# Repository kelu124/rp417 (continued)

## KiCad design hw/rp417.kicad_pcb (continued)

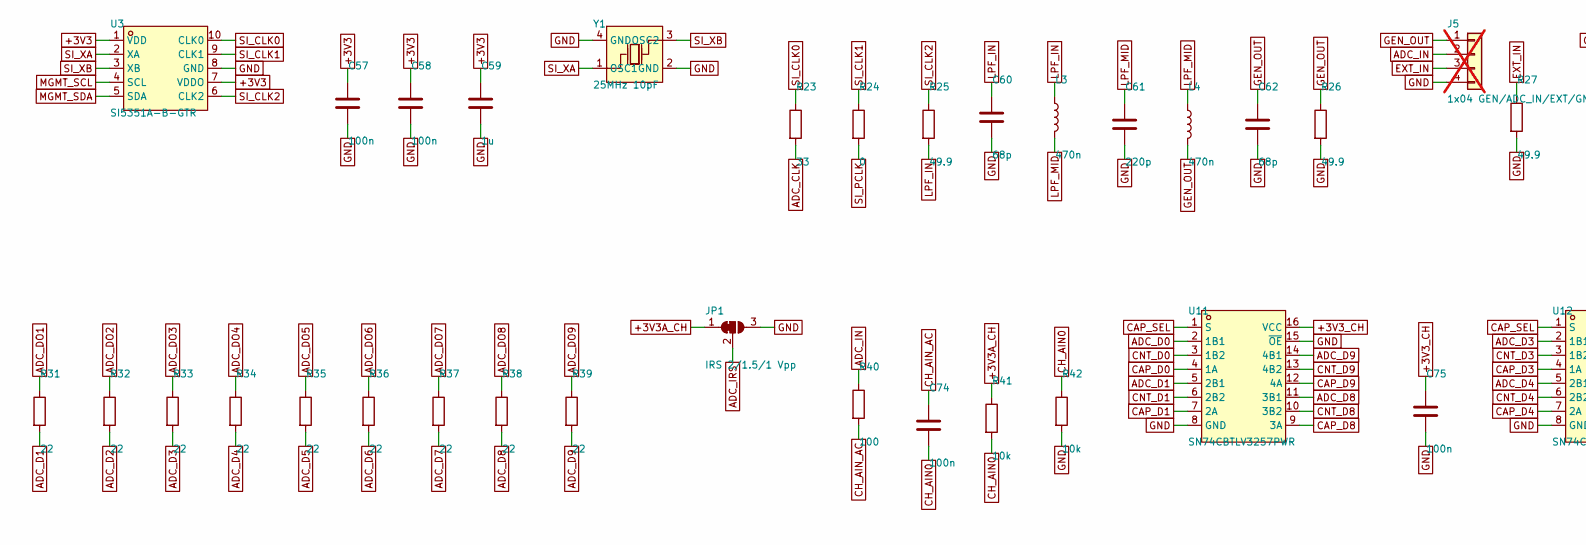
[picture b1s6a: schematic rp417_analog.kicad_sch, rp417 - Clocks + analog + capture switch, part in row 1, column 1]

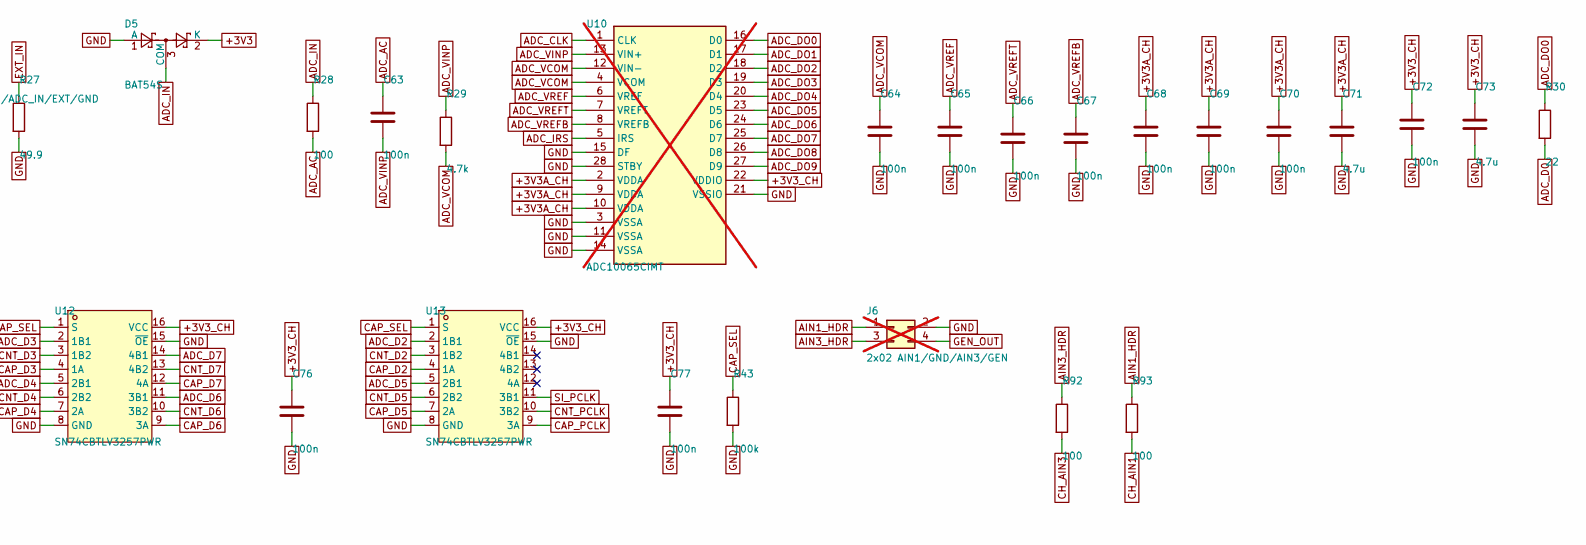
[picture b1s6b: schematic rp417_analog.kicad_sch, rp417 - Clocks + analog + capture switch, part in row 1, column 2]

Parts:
C57, C58, C63, C64, C65, C66, C67, C68, C69, C70, C72, C74, C75, C76, C77: 100n; C_0402_1005Metric; MPN 100n; LCSC C307331
C59: 1u; C_0402_1005Metric; MPN 1u; LCSC C52923
C60, C62: 68p; C_0402_1005Metric; MPN 68p; LCSC C14441
C61: 220p; C_0402_1005Metric; MPN 220p; LCSC C1513258
C71, C73: 4.7u; C_0603_1608Metric; MPN 4.7u; LCSC C19666
D5: BAT54S; SOT-23; MPN BAT54S; LCSC C8592
J5: 1x04 GEN/ADC_IN/EXT/GND; PinHeader_1x04_P2.54mm_Vertical; MPN 1x04 GEN/ADC_IN/EXT/GND; not fitted
J6: 2x02 AIN1/GND/AIN3/GEN; PinHeader_2x02_P2.54mm_Vertical; MPN 2x02 AIN1/GND/AIN3/GEN; not fitted
JP1: IRS 2/1.5/1 Vpp; SolderJumper-3_P1.3mm_Bridged12_RoundedPad1.0x1.5mm; MPN IRS 2/1.5/1 Vpp
L3, L4: 470n; L_0603_1608Metric; MPN LQW18ANR47G00D; LCSC C113132
R23: 33; R_0402_1005Metric; MPN 33; LCSC C25105
R24: 0; R_0402_1005Metric; MPN 0; LCSC C17168
R25, R26, R27: 49.9; R_0402_1005Metric; MPN 49.9; LCSC C25120
R28, R40, R92, R93: 100; R_0402_1005Metric; MPN 100; LCSC C25076
R29: 4.7k; R_0402_1005Metric; MPN 4.7k; LCSC C25900
R30, R31, R32, R33, R34, R35, R36, R37, R38, R39: 22; R_0402_1005Metric; MPN 22; LCSC C25092
R41, R42: 10k; R_0402_1005Metric; MPN 10k; LCSC C25744
R43: 100k; R_0402_1005Metric; MPN 100k; LCSC C25741
U3: SI5351A-B-GTR; MSOP-10_L3.0-W3.0-P0.50-LS5.0-BL; MPN SI5351A-B-GTR; LCSC C504891
U10: ADC10065CIMT; TSSOP-28_4.4x9.7mm_P0.65mm; MPN ADC10065CIMT/NOPB (DNP, user-fitted, D4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; LCSC C1542621; not fitted
U11, U12, U13: SN74CBTLV3257PWR; TSSOP-16_L5.0-W4.4-P0.65-LS6.4-BL; MPN SN74CBTLV3257PWR; LCSC C7637
Y1: 25MHz 10pF; CRYSTAL-SMD_4P-L3.2-W2.5-BL; MPN X322525MMB4SI; LCSC C70582

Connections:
+3V3: C57.1, C58.1, C59.1, D5.2 (K), U3.1 (VDD), U3.7 (VDDO); also elsewhere on the board
+3V3A_CH: C68.1, C69.1, C70.1, C71.1, JP1.1 (A), R41.1, U10.2 (VDDA), U10.9 (VDDA), U10.10 (VDDA); also elsewhere on the board
+3V3_CH: C72.1, C73.1, C75.1, C76.1, C77.1, U10.22 (VDDIO), U11.16 (VCC), U12.16 (VCC), U13.16 (VCC); also elsewhere on the board
ADC_AC: C63.1, R28.2
ADC_CLK: R23.2, U10.1 (CLK)
ADC_D0: R30.2, U11.2 (1B1)
ADC_D1: R31.2, U11.5 (2B1)
ADC_D2: R32.2, U13.2 (1B1)
ADC_D3: R33.2, U12.2 (1B1)
ADC_D4: R34.2, U12.5 (2B1)
ADC_D5: R35.2, U13.5 (2B1)
ADC_D6: R36.2, U12.11 (3B1)
ADC_D7: R37.2, U12.14 (4B1)
ADC_D8: R38.2, U11.11 (3B1)
ADC_D9: R39.2, U11.14 (4B1)
ADC_DO0: R30.1, U10.16 (D0)
ADC_DO1: R31.1, U10.17 (D1)
ADC_DO2: R32.1, U10.18 (D2)
ADC_DO3: R33.1, U10.19 (D3)
ADC_DO4: R34.1, U10.20 (D4)
ADC_DO5: R35.1, U10.23 (D5)
ADC_DO6: R36.1, U10.24 (D6)
ADC_DO7: R37.1, U10.25 (D7)
ADC_DO8: R38.1, U10.26 (D8)
ADC_DO9: R39.1, U10.27 (D9)
ADC_IN: D5.3 (COM), J5.2, R28.1, R40.1
ADC_IRS: JP1.2 (C), U10.5 (IRS)
ADC_VCOM: C64.1, R29.2, U10.4 (VCOM), U10.12 (VIN-)
ADC_VINP: C63.2, R29.1, U10.13 (VIN+)
ADC_VREF: C65.1, U10.6 (VREF)
ADC_VREFB: C67.1, U10.8 (VREFB)
ADC_VREFT: C66.1, U10.7 (VREFT)
AIN1_HDR: J6.1, R93.1
AIN3_HDR: J6.3, R92.1
CAP_D0: U11.4 (1A); also elsewhere on the board
CAP_D1: U11.7 (2A); also elsewhere on the board
CAP_D2: U13.4 (1A); also elsewhere on the board
CAP_D3: U12.4 (1A); also elsewhere on the board
CAP_D4: U12.7 (2A); also elsewhere on the board
CAP_D5: U13.7 (2A); also elsewhere on the board
CAP_D6: U12.9 (3A); also elsewhere on the board
CAP_D7: U12.12 (4A); also elsewhere on the board
CAP_D8: U11.9 (3A); also elsewhere on the board
CAP_D9: U11.12 (4A); also elsewhere on the board
CAP_PCLK: U13.9 (3A); also elsewhere on the board
CAP_SEL: R43.1, U11.1 (S), U12.1 (S), U13.1 (S); also elsewhere on the board
CH_AIN0: C74.2, R41.2, R42.1; also elsewhere on the board
CH_AIN1: R93.2; also elsewhere on the board
CH_AIN3: R92.2; also elsewhere on the board
CH_AIN_AC: C74.1, R40.2
CNT_D0: U11.3 (1B2); also elsewhere on the board
CNT_D1: U11.6 (2B2); also elsewhere on the board
CNT_D2: U13.3 (1B2); also elsewhere on the board
CNT_D3: U12.3 (1B2); also elsewhere on the board
CNT_D4: U12.6 (2B2); also elsewhere on the board
CNT_D5: U13.6 (2B2); also elsewhere on the board
CNT_D6: U12.10 (3B2); also elsewhere on the board
CNT_D7: U12.13 (4B2); also elsewhere on the board
CNT_D8: U11.10 (3B2); also elsewhere on the board
CNT_D9: U11.13 (4B2); also elsewhere on the board
CNT_PCLK: U13.10 (3B2); also elsewhere on the board
EXT_IN: J5.3, R27.1
GEN_OUT: C62.1, J5.1, J6.4, L4.2, R26.1
GND: C57.2, C58.2, C59.2, C60.2, C61.2, C62.2, C64.2, C65.2, C66.2, C67.2, C68.2, C69.2, C70.2, C71.2, C72.2, C73.2, C75.2, C76.2, C77.2, D5.1 (A), J5.4, J6.2, JP1.3 (B), R26.2, R27.2, R42.2, R43.2, U3.8 (GND), U10.3 (VSSA), U10.11 (VSSA), U10.14 (VSSA), U10.15 (DF), U10.21 (VSSIO), U10.28 (STBY), U11.8 (GND), U11.15 (~OE), U12.8 (GND), U12.15 (~OE), U13.8 (GND), U13.15 (~OE), Y1.2 (GND), Y1.4 (GND); also elsewhere on the board
LPF_IN: C60.1, L3.1, R25.2
LPF_MID: C61.1, L3.2, L4.1
MGMT_SCL: U3.4 (SCL); also elsewhere on the board
MGMT_SDA: U3.5 (SDA); also elsewhere on the board
SI_CLK0: R23.1, U3.10 (CLK0)
SI_CLK1: R24.1, U3.9 (CLK1)
SI_CLK2: R25.1, U3.6 (CLK2)
SI_PCLK: R24.2, U13.11 (3B1)
SI_XA: U3.2 (XA), Y1.1 (OSC1)
SI_XB: U3.3 (XB), Y1.3 (OSC2)

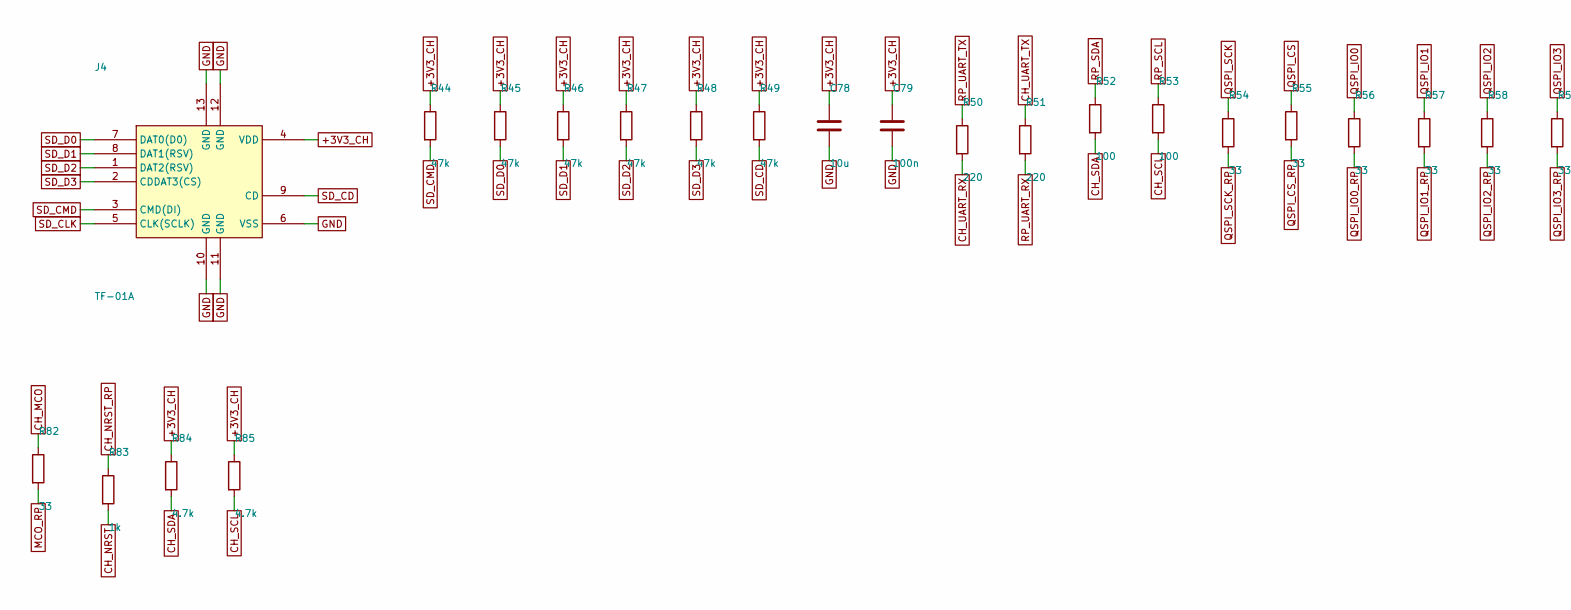
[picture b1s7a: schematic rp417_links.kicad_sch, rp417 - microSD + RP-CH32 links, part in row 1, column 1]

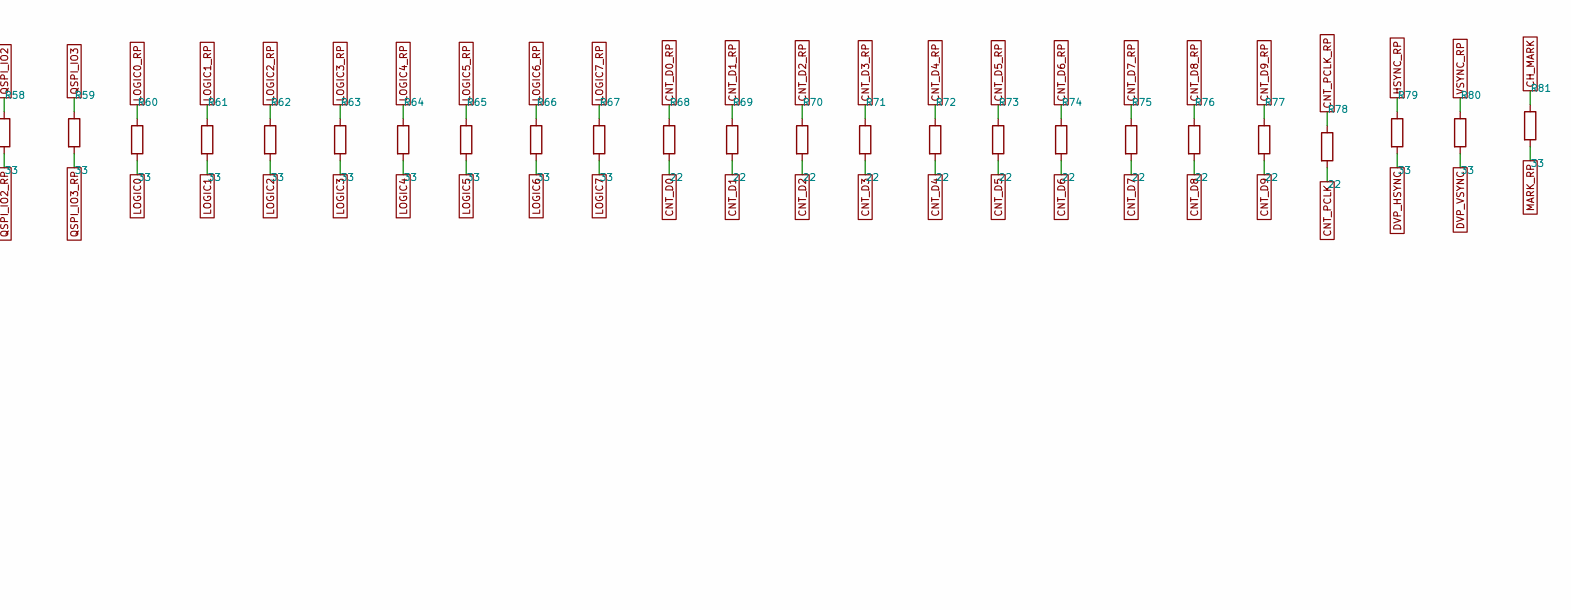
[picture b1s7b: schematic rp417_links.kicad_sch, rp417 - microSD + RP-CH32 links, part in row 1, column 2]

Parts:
C78: 10u; C_0603_1608Metric; MPN 10u; LCSC C96446
C79: 100n; C_0402_1005Metric; MPN 100n; LCSC C307331
J4: TF-01A; TF-SMD_TF-01A; MPN TF-01A; LCSC C91145
R44, R45, R46, R47, R48, R49: 47k; R_0402_1005Metric; MPN 47k; LCSC C25792
R50, R51: 220; R_0402_1005Metric; MPN 220; LCSC C25091
R52, R53: 100; R_0402_1005Metric; MPN 100; LCSC C25076
R54, R55, R56, R57, R58, R59, R60, R61, R62, R63, R64, R65, R66, R67, R79, R80, R81, R82: 33; R_0402_1005Metric; MPN 33; LCSC C25105
R68, R69, R70, R71, R72, R73, R74, R75, R76, R77, R78: 22; R_0402_1005Metric; MPN 22; LCSC C25092
R83: 1k; R_0402_1005Metric; MPN 1k; LCSC C11702
R84, R85: 4.7k; R_0402_1005Metric; MPN 4.7k; LCSC C25900

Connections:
+3V3_CH: C78.1, C79.1, J4.4 (VDD), R44.1, R45.1, R46.1, R47.1, R48.1, R49.1, R84.1, R85.1; also elsewhere on the board
CH_MARK: R81.1; also elsewhere on the board
CH_MCO: R82.1; also elsewhere on the board
CH_NRST: R83.2; also elsewhere on the board
CH_NRST_RP: R83.1; also elsewhere on the board
CH_SCL: R53.2, R85.2; also elsewhere on the board
CH_SDA: R52.2, R84.2; also elsewhere on the board
CH_UART_RX: R50.2; also elsewhere on the board
CH_UART_TX: R51.1; also elsewhere on the board
CNT_D0: R68.2; also elsewhere on the board
CNT_D0_RP: R68.1; also elsewhere on the board
CNT_D1: R69.2; also elsewhere on the board
CNT_D1_RP: R69.1; also elsewhere on the board
CNT_D2: R70.2; also elsewhere on the board
CNT_D2_RP: R70.1; also elsewhere on the board
CNT_D3: R71.2; also elsewhere on the board
CNT_D3_RP: R71.1; also elsewhere on the board
CNT_D4: R72.2; also elsewhere on the board
CNT_D4_RP: R72.1; also elsewhere on the board
CNT_D5: R73.2; also elsewhere on the board
CNT_D5_RP: R73.1; also elsewhere on the board
CNT_D6: R74.2; also elsewhere on the board
CNT_D6_RP: R74.1; also elsewhere on the board
CNT_D7: R75.2; also elsewhere on the board
CNT_D7_RP: R75.1; also elsewhere on the board
CNT_D8: R76.2; also elsewhere on the board
CNT_D8_RP: R76.1; also elsewhere on the board
CNT_D9: R77.2; also elsewhere on the board
CNT_D9_RP: R77.1; also elsewhere on the board
CNT_PCLK: R78.2; also elsewhere on the board
CNT_PCLK_RP: R78.1; also elsewhere on the board
DVP_HSYNC: R79.2; also elsewhere on the board
DVP_VSYNC: R80.2; also elsewhere on the board
GND: C78.2, C79.2, J4.6 (VSS), J4.10 (GND), J4.11 (GND), J4.12 (GND), J4.13 (GND); also elsewhere on the board
HSYNC_RP: R79.1; also elsewhere on the board
LOGIC0: R60.2; also elsewhere on the board
LOGIC0_RP: R60.1; also elsewhere on the board
LOGIC1: R61.2; also elsewhere on the board
LOGIC1_RP: R61.1; also elsewhere on the board
LOGIC2: R62.2; also elsewhere on the board
LOGIC2_RP: R62.1; also elsewhere on the board
LOGIC3: R63.2; also elsewhere on the board
LOGIC3_RP: R63.1; also elsewhere on the board
LOGIC4: R64.2; also elsewhere on the board
LOGIC4_RP: R64.1; also elsewhere on the board
LOGIC5: R65.2; also elsewhere on the board
LOGIC5_RP: R65.1; also elsewhere on the board
LOGIC6: R66.2; also elsewhere on the board
LOGIC6_RP: R66.1; also elsewhere on the board
LOGIC7: R67.2; also elsewhere on the board
LOGIC7_RP: R67.1; also elsewhere on the board
MARK_RP: R81.2; also elsewhere on the board
MCO_RP: R82.2; also elsewhere on the board
QSPI_CS: R55.1; also elsewhere on the board
QSPI_CS_RP: R55.2; also elsewhere on the board
QSPI_IO0: R56.1; also elsewhere on the board
QSPI_IO0_RP: R56.2; also elsewhere on the board
QSPI_IO1: R57.1; also elsewhere on the board
QSPI_IO1_RP: R57.2; also elsewhere on the board
QSPI_IO2: R58.1; also elsewhere on the board
QSPI_IO2_RP: R58.2; also elsewhere on the board
QSPI_IO3: R59.1; also elsewhere on the board
QSPI_IO3_RP: R59.2; also elsewhere on the board
QSPI_SCK: R54.1; also elsewhere on the board
QSPI_SCK_RP: R54.2; also elsewhere on the board
RP_SCL: R53.1; also elsewhere on the board
RP_SDA: R52.1; also elsewhere on the board
RP_UART_RX: R51.2; also elsewhere on the board
RP_UART_TX: R50.1; also elsewhere on the board
SD_CD: J4.9 (CD), R49.2; also elsewhere on the board
SD_CLK: J4.5 (CLK(SCLK)); also elsewhere on the board
SD_CMD: J4.3 (CMD(DI)), R44.2; also elsewhere on the board
SD_D0: J4.7 (DAT0(D0)), R45.2; also elsewhere on the board
SD_D1: J4.8 (DAT1(RSV)), R46.2; also elsewhere on the board
SD_D2: J4.1 (DAT2(RSV)), R47.2; also elsewhere on the board
SD_D3: J4.2 (CDDAT3(CS)), R48.2; also elsewhere on the board
VSYNC_RP: R80.1; also elsewhere on the board

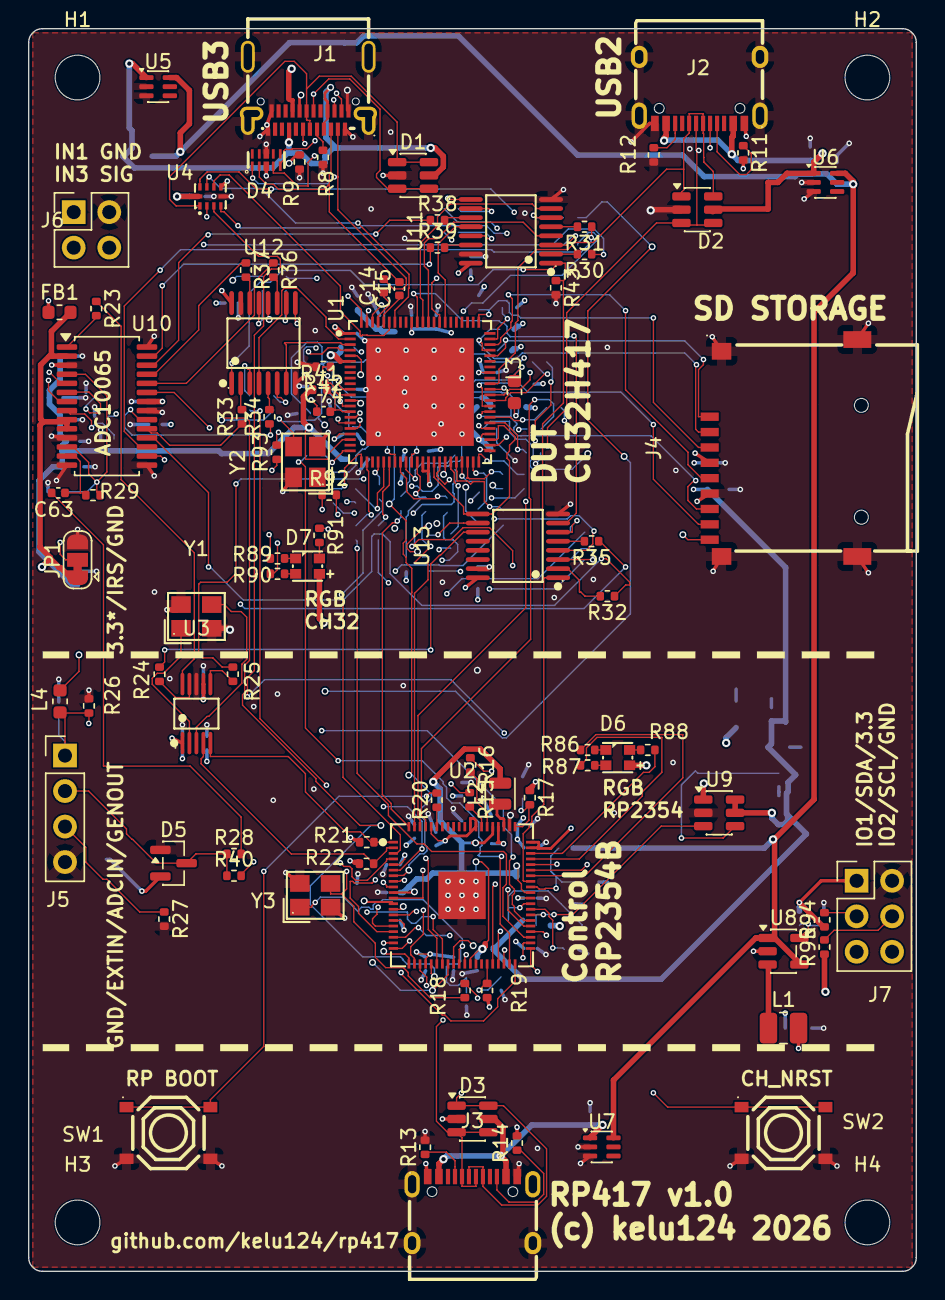
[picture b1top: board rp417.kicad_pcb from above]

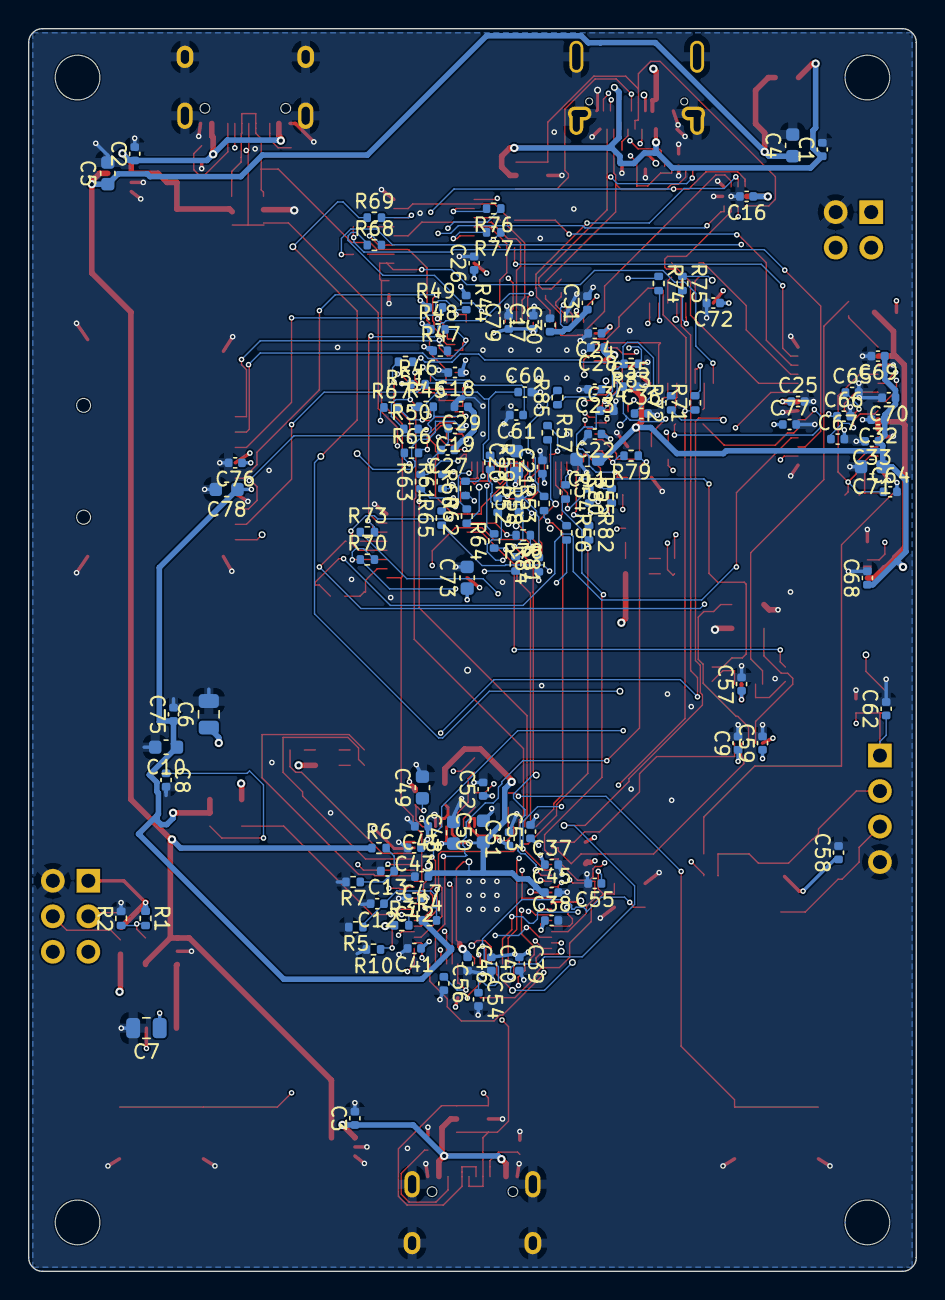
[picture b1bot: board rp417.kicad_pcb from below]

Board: 6 copper layers, 63.5 x 88.9 mm, 216 parts (125 on the bottom side), 200 nets.

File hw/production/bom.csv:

Designator,Footprint,Quantity,Value,LCSC Part #
"C1, C2, C3, C33, C59, C9",0402,6,1u,C52923
"C10, C20, C4, C5, C78",0603,5,10u,C96446
"C11, C48, C49, C50, C71, C73",0603,6,4.7u,C19666
"C12, C13, C14, C15, C16, C17, C18, C19, C21, C22, C23, C24, C25, C27, C28, C30, C32, C36, C37, C38, C39, C40, C41, C42, C43, C44, C45, C46, C47, C51, C52, C53, C56, C57, C58, C63, C64, C65, C66, C67, C68, C69, C70, C72, C74, C75, C76, C77, C79",0402,49,100n,C307331
"C26, C29, C31",0402,3,2.2u,C12530
"C34, C35",0402,2,18p,C1549
"C54, C55",0402,2,15p,C1548
"C6, C7",0805,2,22u,C45783
"C60, C62",0402,2,68p,C14441
C61,0402,1,220p,C1513258
C8,0402,1,1n,C1523
"D1, D2, D3",SOT-23-6,3,USBLC6-2SC6,C7519
D4,SLP2510P8_L2.5-W1.0-P0.50-BL,1,RClamp0524PATCT,C40960
D5,SOT-23,1,BAT54S,C8592
"D6, D7",LED-ARRAY-SMD_4P-L2.1-W2.1-TL_NH-B2020RGBA,2,NH-B2020RGBA-HF,C2874116
FB1,0603,1,600R@100MHz,C1002
J1,USB-C-SMD_TYPE-C-24P-QT,1,TYPE-C 24P QT,C2681555
"J2, J3",USB-C-SMD_TYPE-C-16PIN-2MD-073,2,TYPE-C 16PIN 2MD(073),C2765186
J4,TF-SMD_TF-01A,1,TF-01A,C91145
L1,1008,1,2.2u,C576403
L2,L_Abracon_AOTA-B201610S,1,3.3u,C42411119
"L3, L4",0603,2,470n,C113132
"R1, R10, R3, R4, R43, R5, R6",0402,7,100k,C25741
"R11, R12, R13, R14, R8, R9",0402,6,5.1k,C25905
"R15, R16",0402,2,27,C25100
"R17, R23, R54, R55, R56, R57, R58, R59, R60, R61, R62, R63, R64, R65, R66, R67, R79, R80, R81, R82",0402,20,33,C25105
"R18, R20, R83, R86, R87, R89, R90",0402,7,1k,C11702
"R19, R41, R42",0402,3,10k,C25744
R2,0402,1,22k,C25768
"R21, R22, R29, R84, R85, R94, R95",0402,7,4.7k,C25900
R24,0402,1,0,C17168
"R25, R26, R27",0402,3,49.9,C25120
"R28, R40, R52, R53, R92, R93",0402,6,100,C25076
"R30, R31, R32, R33, R34, R35, R36, R37, R38, R39, R68, R69, R70, R71, R72, R73, R74, R75, R76, R77, R78",0402,21,22,C25092
"R44, R45, R46, R47, R48, R49",0402,6,47k,C25792
"R50, R51",0402,2,220,C25091
R7,0402,1,56k,C25796
"R88, R91",0402,2,330,C25104
SW1,SW-SMD_4P-L5.1-W5.1-P3.70-LS6.5-TL_H1.5,1,BOOTSEL,C318884
SW2,SW-SMD_4P-L5.1-W5.1-P3.70-LS6.5-TL_H1.5,1,RESET,C318884
U1,QFN-88_L10.0-W10.0-P0.40-BL-EP7.7,1,CH32H417MEU6,C54973456
"U11, U12, U13",TSSOP-16_L5.0-W4.4-P0.65-LS6.4-BL,3,SN74CBTLV3257PWR,C7637
U2,QFN-80_L10.0-W10.0-P0.40-TL-EP3.4,1,RP2354B,C39843328
U3,MSOP-10_L3.0-W3.0-P0.50-LS5.0-BL,1,SI5351A-B-GTR,C504891
U4,UQFN-10_L2.0-W1.5-P0.50-BL,1,TS3USB221ARSER,C128396
"U5, U6, U7",SOT-363_SC-70-6,3,LM66100DCKR,C2869734
U8,SOT-23-5,1,TLV62569DBVR,C141836
U9,SOT-23-6,1,TPS22918DBVR,C131941
Y1,CRYSTAL-SMD_4P-L3.2-W2.5-BL,1,25MHz 10pF,C50430
Y2,CRYSTAL-SMD_4P-L3.2-W2.5-BL,1,25MHz 12pF,C50430
Y3,CRYSTAL-SMD_4P-L3.2-W2.5-BL,1,12MHz 10pF,C50430

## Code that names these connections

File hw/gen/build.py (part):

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   lcsc="C40960")
ic("D1", "USBLC6", "USBLC6-2SC6", "Package_TO_SOT_SMD:SOT-23-6",
   by_num={"1": "J1_DP", "6": "J1_DP", "3": "J1_DM", "4": "J1_DM", "2": "GND", "5": "VBUS1"}, lcsc="C7519")
# USB2 switch on PB8/PB9 (D14, D26): S=0 -> 1D (connector), S=1 -> 2D (RP SWD)
ic("U4", "TS3", "TS3USB221ARSER", "lcsc:UQFN-10_L2.0-W1.5-P0.50-BL",
   by_name={"1D+": "J1_DP", "1D-": "J1_DM", "2D+": "SWCLK_RP", "2D-": "SWIO_RP", "GND": "GND",
            "~{OE}": "GND", "D+": "CH_USBHS_DP", "D-": "CH_USBHS_DM", "S": "USB_SEL", "VCC": "+3V3"},
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    "VDDK": "VDDK", "VDD12A": "VDD12A",
    "XI": "CH_XI", "XO": "CH_XO", "NRST": "CH_NRST",
    # DVP, one pin set fed by the 2:1 capture switch (D55): ADC10065 or RP counter
    "PE0": "CAP_D0", "PE1": "CAP_D1", "PB13": "CAP_D2", "PE3": "CAP_D3", "PE4": "CAP_D4", "PF14": "CAP_D5",
    "PE5": "CAP_D6", "PE6": "CAP_D7", "PF4": "CAP_D8", "PF3": "CAP_D9", "PB12": "CAP_PCLK",
    "PF2": "CAP_PCLK",                 # TIM8_ETR (AF3): sample counter
    "PA4": "DVP_HSYNC", "PA5": "DVP_VSYNC",
    # RP<->CH32 logic bus, general GPIO (D03)
    "PD12": "LOGIC0", "PD13": "LOGIC1", "PD14": "LOGIC2", "PD15": "LOGIC3", "PD10": "LOGIC4", "PD11": "LOGIC5",
    "PC6": "LOGIC6", "PC7": "LOGIC7",
    "PC0": "CH_AIN0",
    "PC1": "CH_AIN1",                  # D65 HSADC_IN1 / ADC_IN11, on J6 via 100R
    "PC3": "CH_AIN3",                  # D64 HSADC_IN3 / ADC_IN13, on J6 via 100R
    "PC2": "LED_CH_R", "PF0": "LED_CH_G", "PF1": "LED_CH_B",   # D62/D63 status LED (pins 17, 45, 46)
    # microSD (D04), SDMMC_RM=00
    "PD2": "SD_CMD", "PC12": "SD_CLK", "PC8": "SD_D0", "PC9": "SD_D1", "PC10": "SD_D2", "PC11": "SD_D3",
    "PD0": "SD_CD",
    # QSPI2 master (D38)
    "PE10": "QSPI_SCK", "PE11": "QSPI_CS", "PE12": "QSPI_IO0", "PE13": "QSPI_IO1", "PE14": "QSPI_IO2",
    "PE15": "QSPI_IO3",
    "PA9": "CH_UART_TX", "PA10": "CH_UART_RX",   # USART1 = UART ISP pins on QFN88 (EVB ref.)
    "PB10": "CH_SCL", "PB11": "CH_SDA",
    "PB14": "CH_MARK",                 # TIM9_CH1 (AF2)
    "PB0": "CH_MCO",
    "PB8": "CH_USBHS_DP", "PB9": "CH_USBHS_DM", "PA11": "J2_DM", "PA12": "J2_DP",
    "SSTXA": "CH_SSTX_P", "SSTXB": "CH_SSTX_N", "SSRXA": "SS_RX_P", "SSRXB": "SS_RX_N",
}
ic("U1", "CH32", "CH32H417MEU6", "lcsc:QFN-88_L10.0-W10.0-P0.40-BL-EP7.7", by_name=ch, rest=None,
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    "VREG_LX": "RP_VREG_LX", "VREG_FB": "+1V1", "ADC_AVDD": "+3V3", "USB_OTP_VDD": "+3V3",
    "QSPI_IOVDD": "+3V3", "GND": "GND", "XIN": "RP_XIN", "XOUT": "RP_XOUT", "RUN": "RP_RUN",
    "USB_DM": "RP_USB_DM", "USB_DP": "RP_USB_DP", "QSPI_SS": "RP_QSPI_SS",
    "GPIO0": "RP_UART_TX", "GPIO1": "RP_UART_RX", "GPIO2": "RP_SDA", "GPIO3": "RP_SCL",
    "GPIO4": "MGMT_SDA", "GPIO5": "MGMT_SCL",
    "GPIO6": "QSPI_SCK_RP", "GPIO7": "QSPI_CS_RP", "GPIO8": "QSPI_IO0_RP", "GPIO9": "QSPI_IO1_RP",
    "GPIO10": "QSPI_IO2_RP", "GPIO11": "QSPI_IO3_RP",
    **{f"GPIO{12 + i}": f"LOGIC{i}_RP" for i in range(8)},          # GPIO12-19 logic bus
    **{f"GPIO{20 + i}": f"CNT_D{i}_RP" for i in range(10)},         # GPIO20-29 PIO counter D0-D9
    "GPIO30": "CNT_PCLK_RP",                                         # PIO side-set clock
    "GPIO42_ADC2": "CAP_SEL",                                        # 2:1 capture switch select
    "GPIO31": "HSYNC_RP", "GPIO32": "VSYNC_RP", "GPIO33": "MARK_RP", "GPIO34": "MCO_RP",
    "GPIO35": "SWIO_RP", "GPIO36": "SWCLK_RP", "GPIO37": "CH_NRST_RP", "GPIO38": "CH_PWR_EN",
    "GPIO39": "USB_SEL", "GPIO40_ADC0": "ADC_V3V3CH", "GPIO41_ADC1": "ADC_VSYS",
    "GPIO43_ADC3": "LED_RP_R", "GPIO46_ADC6": "LED_RP_G", "GPIO47_ADC7": "LED_RP_B",   # D62 status RGB (R moved to GPIO43, D66)
    "GPIO44_ADC4": "SAO_SDA", "GPIO45_ADC5": "SAO_SCL",                                 # D66 I2C0 on the SAO header
}
ic("U2", "RP", "RP2354B", "lcsc:QFN-80_L10.0-W10.0-P0.40-TL-EP3.4", by_name=rp, rest=None, lcsc="C39843328")
for _ in range(8): C("100n", "+3V3")             # IOVDD x8
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C("68p", "GEN_OUT")
R("49.9", "GEN_OUT", "GND")
# input-select header (D34): 1 GEN, 2 ADC_IN, 3 EXT, 4 GND
ic("J5", "HDR4", "1x04 GEN/ADC_IN/EXT/GND", "Connector_PinHeader_2.54mm:PinHeader_1x04_P2.54mm_Vertical",
   by_num={"1": "GEN_OUT", "2": "ADC_IN", "3": "EXT_IN", "4": "GND"}, dnp=True)   # D68: 2.54 headers DNP
R("49.9", "EXT_IN", "GND")                       # external source termination
ic("D5", "BAT54S", "BAT54S", "Package_TO_SOT_SMD:SOT-23",
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R("330", "LED_RP_B", "LED_RP_BK")
cur = sheets["ch32"]
ic("D7", "RGB", "NH-B2020RGBA-HF", LED_FP, by_num={"3": "+3V3_CH", "1": "LED_CH_RK", "4": "LED_CH_GK", "2": "LED_CH_BK"},
   lcsc="C2874116")                                 # blue on PF1 (D63)
R("1k", "LED_CH_R", "LED_CH_RK")
R("1k", "LED_CH_G", "LED_CH_GK")
R("330", "LED_CH_B", "LED_CH_BK")                  # D63, appended last -> R91

# ---------------------------------------------------------------- D64 HSADC test header
# J6 2x2 2.54 mm: 1 PC1 (HSADC_IN1, via 100R, D65) | 2 GND / 3 PC3 (HSADC_IN3, via 100R) | 4 GEN_OUT.
# Jumper 1-3 = HSADC_IN1 + IN3 tied; jumper 3-4 = raw generator into PC3; 1-2 = IN1 grounded.
cur = sheets["analog"]
ic("J6", "HDR2X2", "2x02 AIN1/GND/AIN3/GEN", "Connector_PinHeader_2.54mm:PinHeader_2x02_P2.54mm_Vertical",
   by_num={"1": "AIN1_HDR", "2": "GND", "3": "AIN3_HDR", "4": "GEN_OUT"}, dnp=True)
R("100", "AIN3_HDR", "CH_AIN3")                   # limits back-feed into PC3 with the CH32 off (D29) -> R92
R("100", "AIN1_HDR", "CH_AIN1")                   # D65, same for PC1 -> R93

# ---------------------------------------------------------------- D66 SAO header (I2C0)
# "Shitty Add-On" v1.69bis 2x3 2.54 mm: 1 VCC | 2 GND / 3 SDA | 4 SCL / 5 GPIO1 | 6 GPIO2.
# RP2350 I2C0 = GPIO44 SDA / GPIO45 SCL. VCC = +3V3 (always-on RP rail, pull-ups on the same rail).
# GPIO1/GPIO2 not connected: no free RP GPIO left (SWD and QSPI pins excluded).
cur = sheets["rp"]
ic("J7", "HDR2X3", "SAO 2x03 VCC/GND/SDA/SCL", "Connector_PinHeader_2.54mm:PinHeader_2x03_P2.54mm_Vertical",
   by_num={"1": "+3V3", "2": "GND", "3": "SAO_SDA", "4": "SAO_SCL", "5": None, "6": None}, dnp=True)
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
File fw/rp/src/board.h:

// rp417 RP2354B supervisor — pin map and board-level control.
// Source of truth for the nets: hw/gen/build.py (docs/pinmap.md).
#pragma once
#include <stdbool.h>
#include <stdint.h>
#include "pico/types.h"

// ---- RP <-> CH32 (all through series R, D29)
#define PIN_UART_TX      0   // RP_UART_TX -> R50 220R -> CH32 PA10 (USART1 RX)
#define PIN_UART_RX      1   // RP_UART_RX <- R51 220R <- CH32 PA9  (USART1 TX)
#define PIN_CH_SDA       2   // I2C1 -> R52 100R -> CH32 PB11 (not used in v0.1)
#define PIN_CH_SCL       3   // I2C1 -> R53 100R -> CH32 PB10 (not used in v0.1)
#define PIN_QSPI_BASE    6   // GPIO6..11 -> CH32 QSPI2 (PE10..PE15), not used in v0.1
#define PIN_LOGIC_BASE  12   // GPIO12..19 = LOGIC0..7 (CH32 PD12 PD13 PD14 PD15 PD10 PD11 PC6 PC7)
#define PIN_CNT_BASE    20   // GPIO20..29 = counter D0..D9 (to capture switch B, D55)
#define PIN_CNT_PCLK    30   // counter PCLK (side-set)
#define PIN_HSYNC       31   // -> CH32 PA4 (DVP HSYNC, D37)
#define PIN_VSYNC       32   // -> CH32 PA5 (DVP VSYNC, D37)
#define PIN_MARK        33   // <- CH32 PB14 (shot marker)
#define PIN_MCO         34   // <- CH32 PB0 (MCO)
#define PIN_SWIO        35   // -> U4 2D- -> CH32 PB9 (SWIO/SWDIO) when USB_SEL = 1
#define PIN_SWCLK       36   // -> U4 2D+ -> CH32 PB8 (SWCLK)      when USB_SEL = 1
#define PIN_CH_NRST     37   // -> R83 1k -> CH32 NRST (open-drain emulation: drive low or float)

// ---- board control
#define PIN_MGMT_SDA     4   // I2C0: Si5351A (0x60)
#define PIN_MGMT_SCL     5
#define PIN_CH_PWR_EN   38   // TPS22918 ON, 100k pull-up (CH32 domain ON by default, D15/D25)
#define PIN_USB_SEL     39   // TS3USB221A S: 0 = CH32 PB8/PB9 on J1 (100k pull-down), 1 = RP SWD
#define PIN_ADC_V3V3CH  40   // ADC0: +3V3_CH / 2   (100k/100k)
#define PIN_ADC_VSYS    41   // ADC1: VSYS * 56/156 (100k/56k)
#define PIN_CAP_SEL     42   // 2:1 capture switches: 0 = ADC10065 (pull-down), 1 = RP counter
#define PIN_LED_R       43   // D6, common anode on +3V3 -> active LOW
#define PIN_SAO_SDA     44   // I2C0 alt pins (SAO header J7) — clashes with MGMT on I2C0, unused in v0.1
#define PIN_SAO_SCL     45
#define PIN_LED_G       46
#define PIN_LED_B       47

#define LED_R 1
#define LED_G 2
#define LED_B 4

void board_init_safe(void);          // standalone defaults (D15): CH32 on, NRST released, USB_SEL=USB
void board_led(uint8_t rgb);

// CH32 power domain (D25/D29). Off: tri-state every RP->CH32 line and stop the Si5351 outputs first.
bool ch_power_is_on(void);
int  ch_power_on(void);              // 0 ok, <0 rail did not come up
int  ch_power_off(void);             // 0 ok, <0 rail did not discharge
void ch_lines_release(void);         // every RP->CH32 output to input (high-Z)
void ch_lines_enable(void);          // UART TX back on (others stay inputs until a test drives them)

void ch_reset_pulse(uint32_t ms);
void ch_reset_hold(bool assert);

void usb_sel_swd(bool swd);          // true = PB8/PB9 to the RP programmer
bool usb_sel_is_swd(void);
void cap_sel_rp(bool rp);            // true = RP counter drives the DVP bus

float adc_v3v3ch(void);
float adc_vsys(void);

uint32_t freq_measure(uint pin, uint32_t gate_ms);   // edges per second on a GPIO in 16..47
